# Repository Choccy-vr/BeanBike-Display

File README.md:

# BeanBike-Display
### Description
A smart display to use with VESC controllers for Hack Club's Goated YSWS Macondo!!
### Demo
Here is a demo video on YouTube. https://youtu.be/hzEWeqmnlWU
### Specs
- ESP32 S3 N16R8
- Waveshare 480x320 capasitive display
- Custom PCB
### Detailed Description
A smart display using an ESP32 S3 and custom-developed firmware to communicate with VESC devices. Built for eBikes, BeanBike-Display can connect to virtually any VESC controller. With a beautiful 480x320 display from Waveshare to pair with UI designed in Squareline Vision and built with LVGL for fast, beautiful UIs. 
### Why I made this
I made this because I love mobility projects (like e-bikes or anything that moves you around); they are just so fun. This is a successor in a way to a previous project where I tried to create my own BLDC controller (it didn't go well), so this time I am making the display with all the smart functionality and VESC)
### BOM
Note that these are the things that I need funded. Everything else I already have. (The build cost on Macondo is outdated, but I couldn't change it. The cart pics are mostly the same, just with some stuff removed)
|Product Name |Product Description  |Product Link                                                                                                                                                                                                                                                                 |Product unit price|Product amount|Product Cost|Total (Before Tax + Shipping)|Total (Without Shipping)|Total |
|-------------|---------------------|-----------------------------------------------------------------------------------------------------------------------------------------------------------------------------------------------------------------------------------------------------------------------------|------------------|--------------|------------|-----------------------------|------------------------|------|
|FPC Connector|Connecting to dosplay|https://www.digikey.com/en/products/detail/molex/5034801800/2819155?s=N4IgTCBcDaIKwAYDMAWAHAgjBhIC6AvkA                                                                                                                                                                      |$1.50             |1             |$1.50       |$8.70                        |$9.31                   |$19.36|
|PCB          |uhh PCB              |https://cart.jlcpcb.com/shopcart/cart                                                                                                                                                                                                                                        |$2                |1             |$2          |                             |                        |      |
|Headers      |connecting to ESP    |https://www.aliexpress.us/item/3256810564318830.html?spm=a2g0o.cart.0.0.213f7a9d2CsPC1&mp=1&pdp_npi=6%40dis%21USD%21USD+5.53%21USD+2.60%21%21USD+2.58%21%21%21%402103212317824399376733356ea018%2112000053390335942%21ct%21US%213108417632%21%212%210%21&gatewayAdapt=glo2usa|$2.60             |2             |$5.20       |                             |                        |      |
### Firmware
Open up the firmware folder in PlatformIO and press upload!
## Images

### UI

#### Mockup

#### Built UI

### PCB

#### Schematic

#### Layout

#### 3D PCB

### Built Images

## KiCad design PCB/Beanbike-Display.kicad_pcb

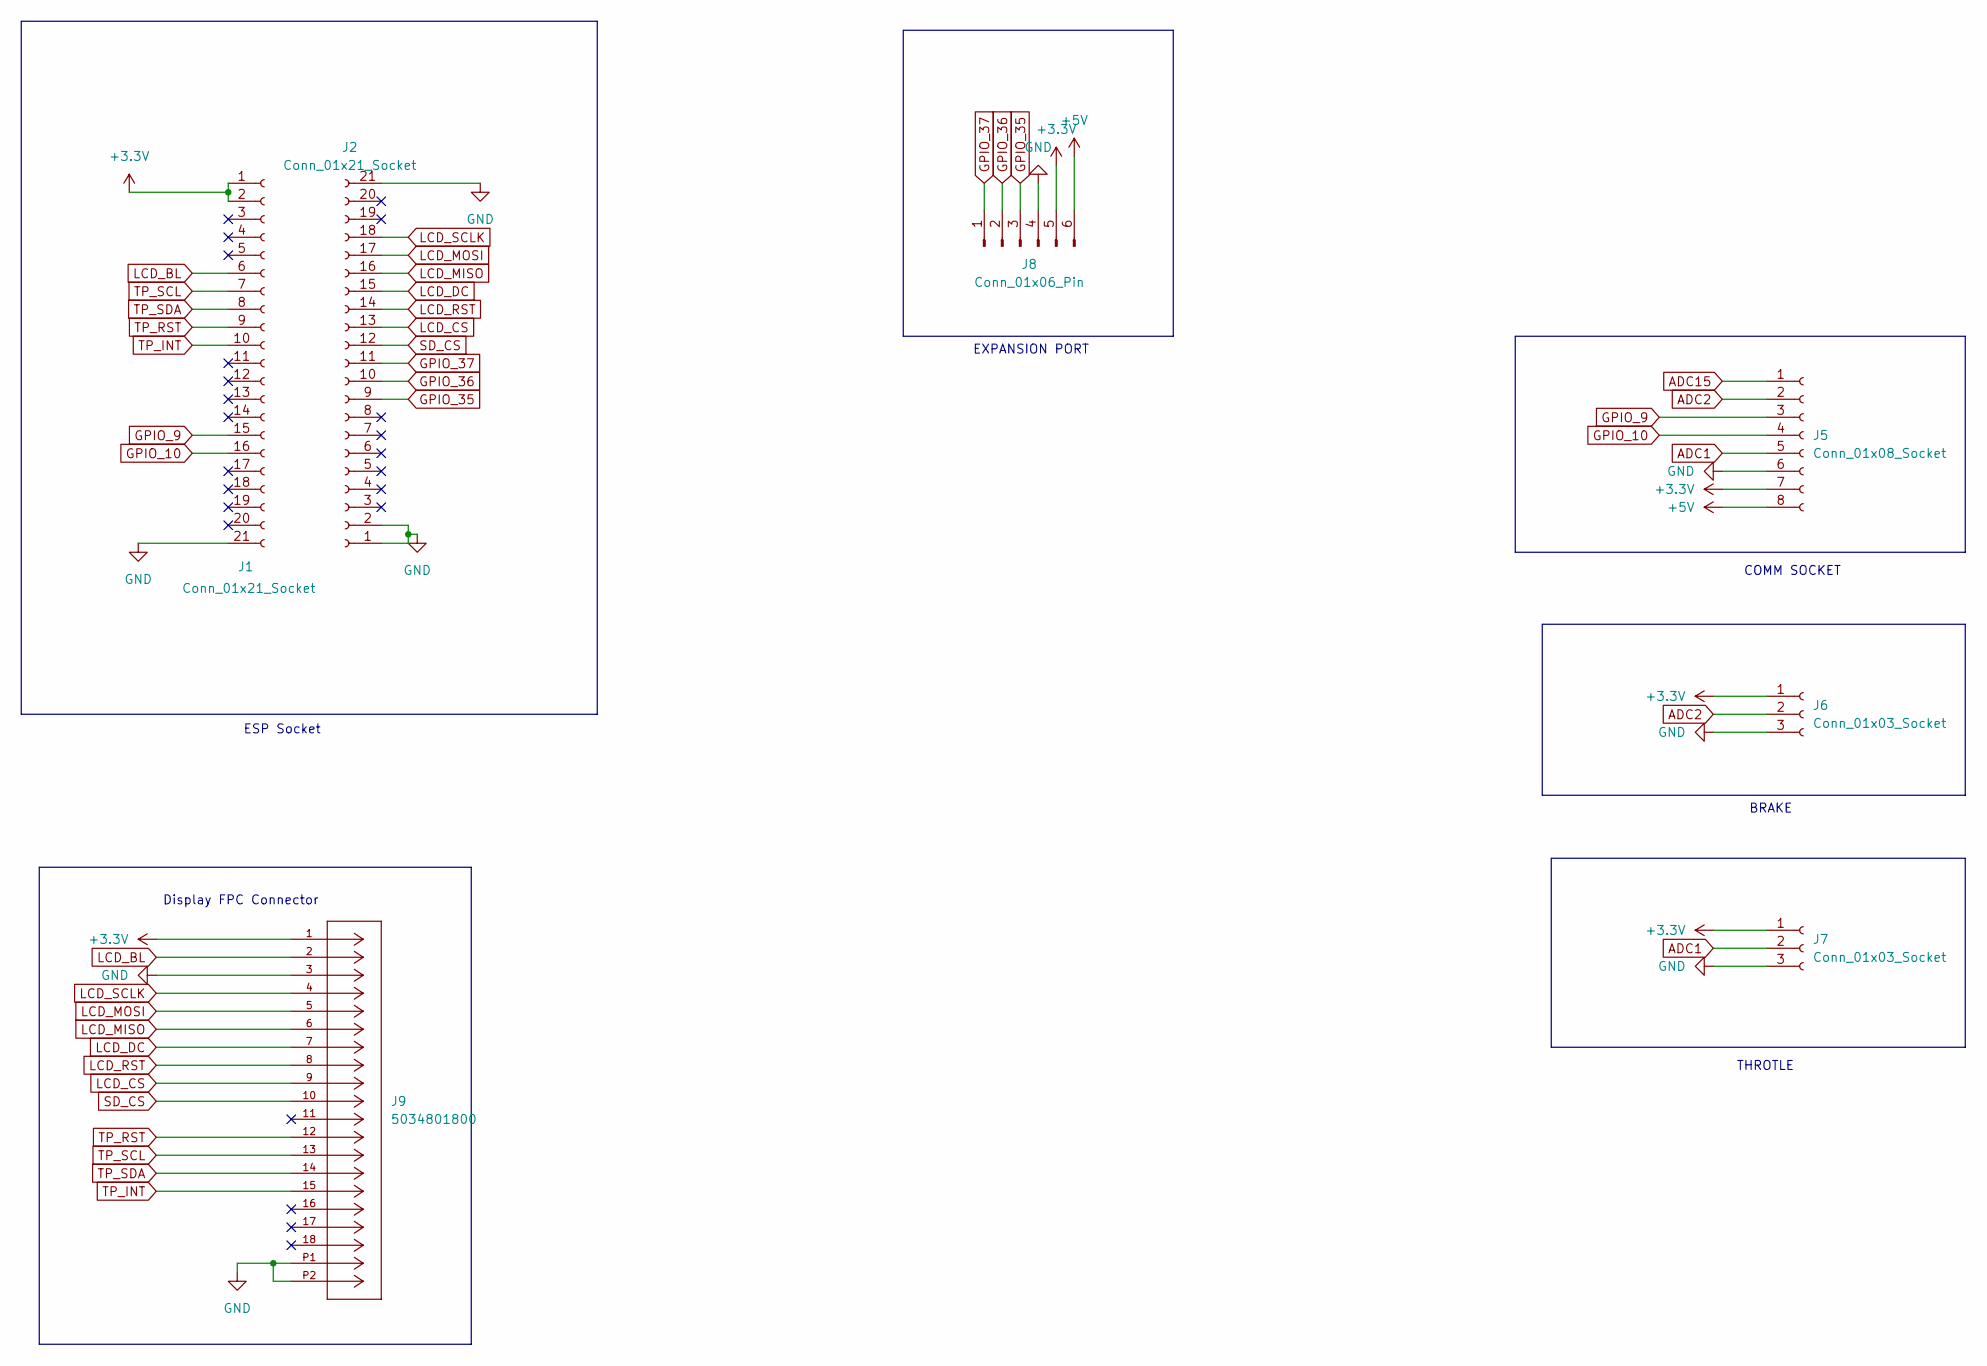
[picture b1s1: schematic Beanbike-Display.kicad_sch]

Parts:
J1, J2: Conn_01x21_Socket; PinSocket_1x21_P2.54mm_Vertical
J5: Conn_01x08_Socket; PinSocket_1x08_P2.54mm_Vertical
J6, J7: Conn_01x03_Socket; PinSocket_1x03_P2.54mm_Vertical
J8: Conn_01x06_Pin; PinHeader_1x06_P2.54mm_Vertical
J9: 5034801800; CON_5034801800_MOL; MANUFACTURER_PART_NUMBER 5034801800

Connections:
+3.3V: J1.1, J1.2, J5.7, J6.1, J7.1, J8.5, J9.1
+5V: J5.8, J8.6
ADC1: J5.5, J7.2
ADC2: J5.2, J6.2
ADC15: J5.1
GND: J1.21, J2.1, J2.2, J2.21, J5.6, J6.3, J7.3, J8.4, J9.3, J9.P1, J9.P2
GPIO_9: J1.15, J5.3
GPIO_10: J1.16, J5.4
GPIO_35: J2.9, J8.3
GPIO_36: J2.10, J8.2
GPIO_37: J2.11, J8.1
LCD_BL: J1.6, J9.2
LCD_CS: J2.13, J9.9
LCD_DC: J2.15, J9.7
LCD_MISO: J2.16, J9.6
LCD_MOSI: J2.17, J9.5
LCD_RST: J2.14, J9.8
LCD_SCLK: J2.18, J9.4
SD_CS: J2.12, J9.10
TP_INT: J1.10, J9.15
TP_RST: J1.9, J9.12
TP_SCL: J1.7, J9.13
TP_SDA: J1.8, J9.14

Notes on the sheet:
EXPANSION PORT
THROTLE
ESP Socket
BRAKE
Display FPC Connector
COMM SOCKET

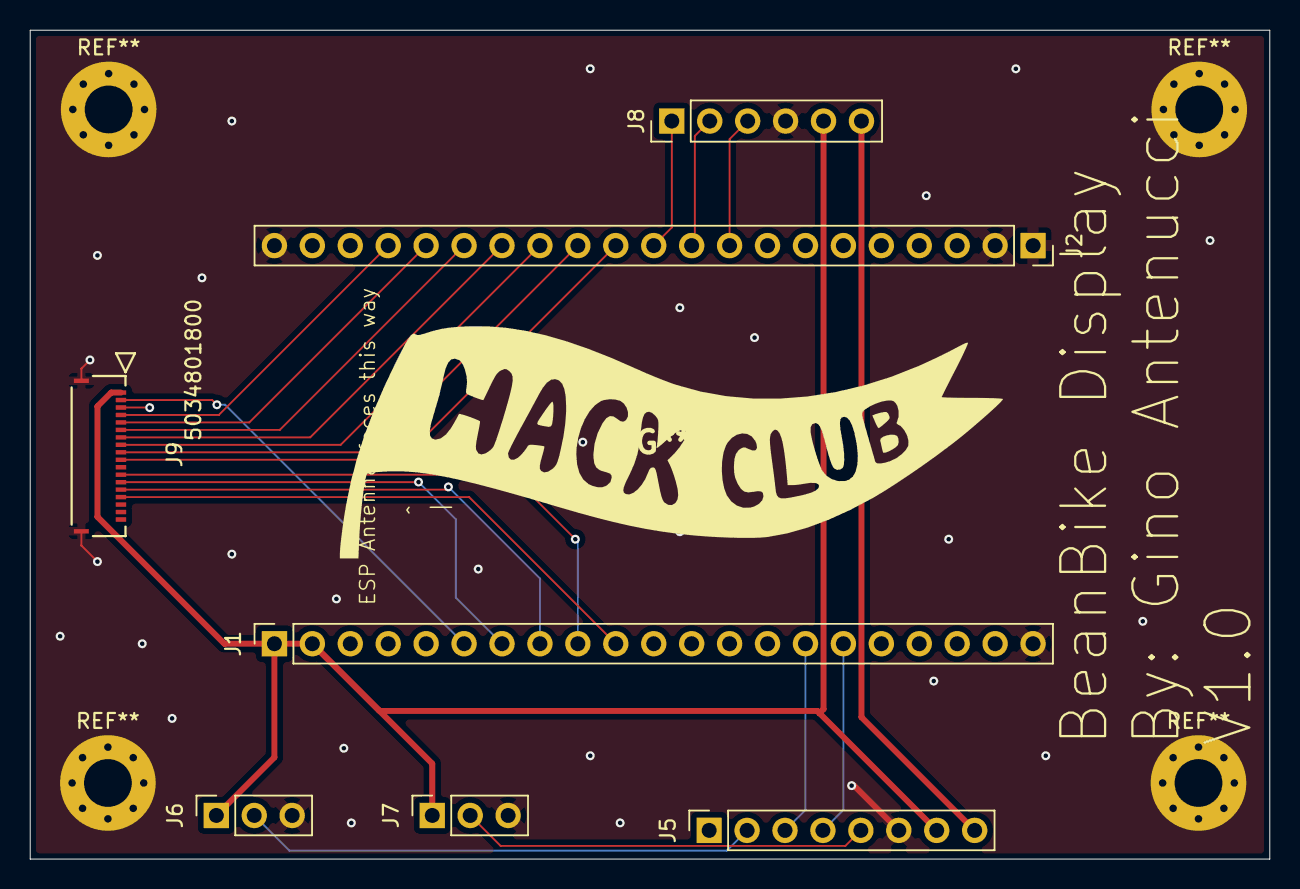
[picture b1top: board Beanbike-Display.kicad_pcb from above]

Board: 2 copper layers, 83.0 x 55.5 mm, 7 parts (0 on the bottom side), 22 nets.

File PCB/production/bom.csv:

Designator,Footprint,Quantity,Value,LCSC Part #
"J1, J2",PinSocket_1x21_P2.54mm_Vertical,2,Conn_01x21_Socket,
J5,PinSocket_1x08_P2.54mm_Vertical,1,Conn_01x08_Socket,
"J6, J7",PinSocket_1x03_P2.54mm_Vertical,2,Conn_01x03_Socket,
J8,PinHeader_1x06_P2.54mm_Vertical,1,Conn_01x06_Pin,
J9,CON_5034801800_MOL,1,5034801800,

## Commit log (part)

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2026-05-23 Add Headers
    Init project and add headers needed to connect to the controller
2026-05-24 PCB v1
2026-05-25 Touchscreen +LVGL
2026-06-03 BikeState & RTOS
    I forgot to commit
2026-06-04 Add images to README
2026-06-26 Add BOM
